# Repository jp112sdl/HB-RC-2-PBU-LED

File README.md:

# HB-RC-2-PBU-LED

**2 fach Wandtaster, ähnlich dem [HmIP-BSL](https://www.elv.de/elv-homematic-ip-schaltaktor-fuer-markenschalter-mit-signalleuchte-hmip-bsl.html), mit RGB LED Beleuchtung (oben/unten)).**

Thread im Homematic Forum: https://homematic-forum.de/forum/viewtopic.php?f=76&t=53254

### Bauteile
| Anzahl | Ref | Typ | Bezeichnung |
|----|----|----|----|
1 | U1 | AVR | [ATMega 328P-AU](https://www.reichelt.de/mcu-atmega-avr-risc-32-kb-20-mhz-tqfp-32-atmega-328p-au-p119684.html)
2 | R1, R2 | Widerstand 330 | [RND 0805 330](https://www.reichelt.de/smd-widerstand-0805-330-ohm-125-mw-1-rnd-0805-1-330-p183184.html)
2 | R3, R4 | Widerstand 10k | [RND 0805 10k](https://www.reichelt.de/smd-widerstand-0805-10-kohm-125-mw-1-rnd-0805-1-10k-p183251.html)
4 | C2, C4, C5, C7 |Kondensator 100n |[X7R-G0805 100N](https://www.reichelt.de/smd-vielschicht-keramikkondensator-100n-10-x7r-g0805-100n-p31879.html)
1 | C1 | ELKO 1µF/50V | [SMD ELKO 1,0/50](https://www.reichelt.de/smd-chip-elko-1-0-f-50volt-smd-elko-1-0-50-p31900.html)
2 | C3, C6 | ELKO 10µF/16V | [SMD ELKO 10/16](https://www.reichelt.de/smd-chip-elko-10-f-16volt-smd-elko-10-16-p31906.html)
1 | U2 | LDO | [TLV1117-33](https://www.reichelt.de/ldo-regler-fest-3-3-v-sot-223-4-tlv-1117-33-cdcy-p188993.html)
1 | D1 | DuoLED 3mm | [RND 135-00023](https://www.reichelt.de/led-3-mm-bedrahtet-rot-gruen-20-mcd-40-rnd-135-00023-p224130.html)
1 | U3 | LevelShifter | [SN74LVC1T45DBVR](https://www.aliexpress.com/item/32963167201.html)
1 | IC1 | 868MHz Funkmodul | [CC1101](https://www.aliexpress.com/item/32924239954.html)
1 | SW1, SW2, SW3 | Taster | [Tastersortiment](https://www.aliexpress.com/item/32811153729.html)
2 | |WS2812B LED Streifen | [NeoPixel-Stick-WS2812](https://www.amazon.de/NeoPixel-Stick-WS2812-5050-LEDs/dp/B019ZKN3XQ)

### PCB

### ein paar Bilder

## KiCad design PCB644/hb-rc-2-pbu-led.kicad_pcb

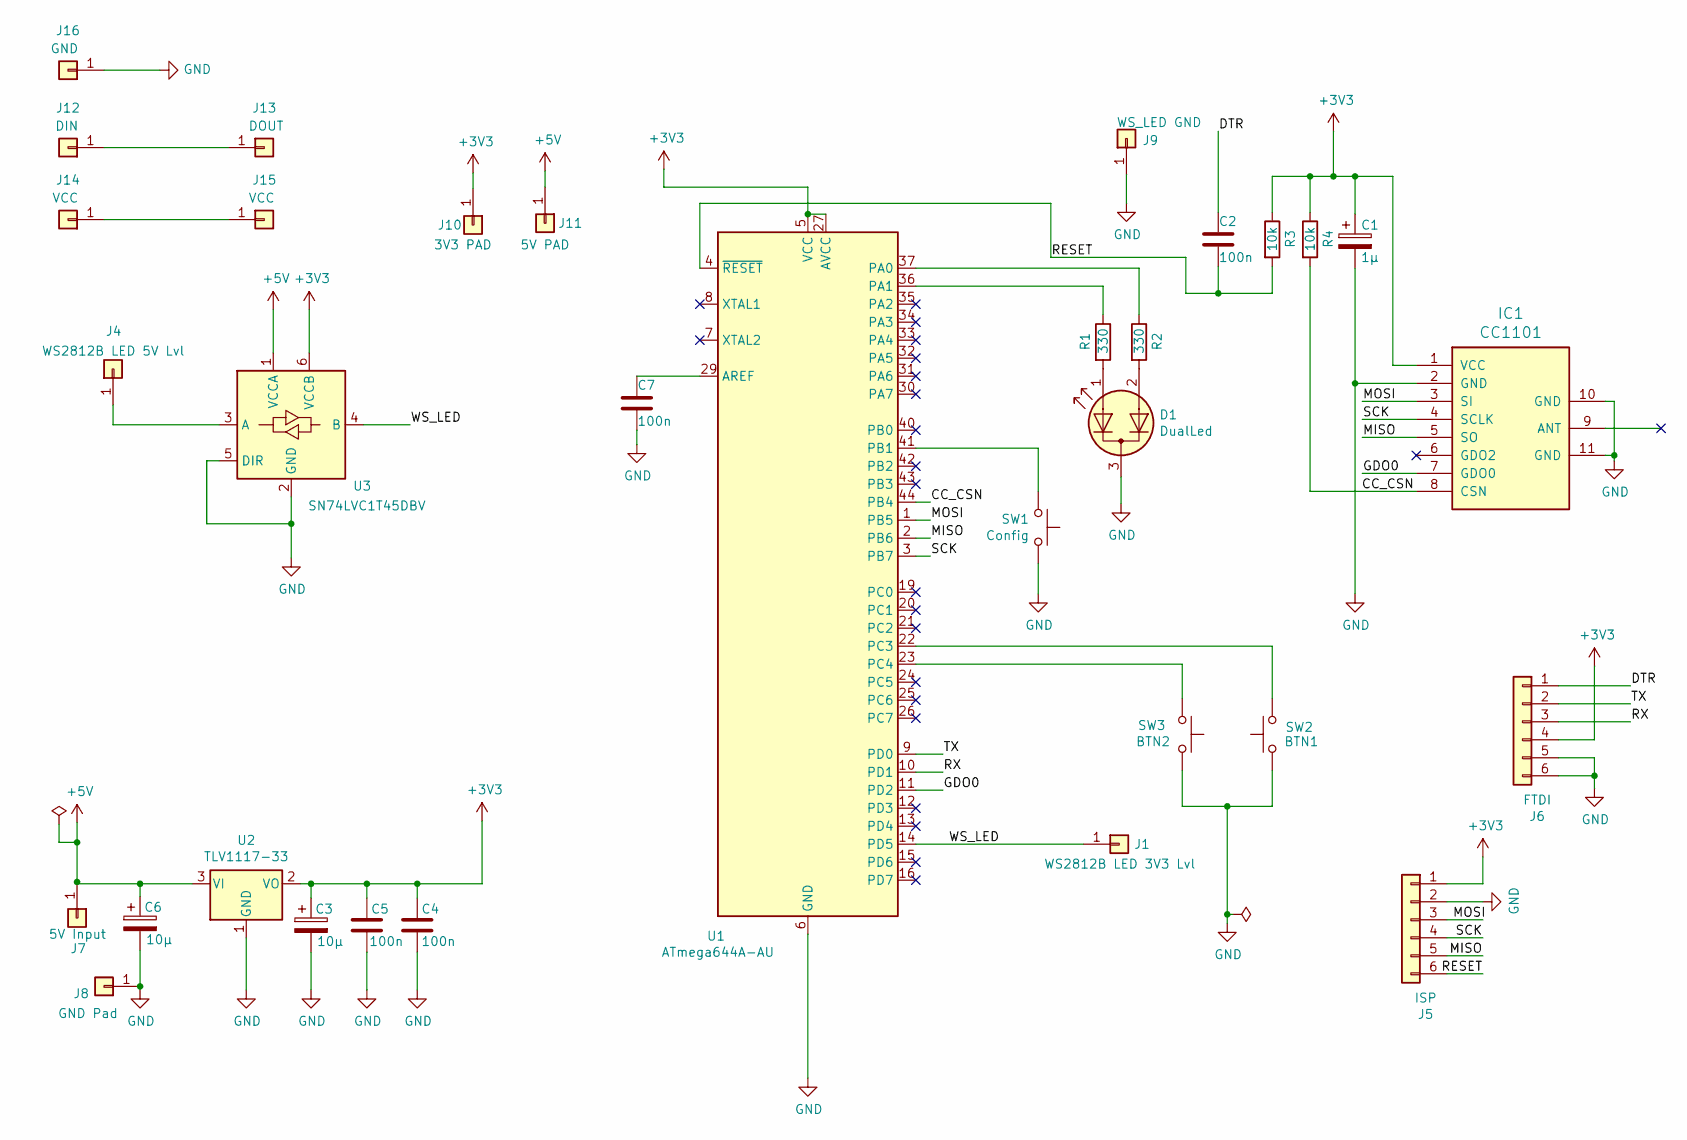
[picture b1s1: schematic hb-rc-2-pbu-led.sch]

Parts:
C1: 1µ; CP_Elec_4x5.3
C2, C4, C5, C7: 100n; C_0805_2012Metric_Pad1.15x1.40mm_HandSolder
C3, C6: 10µ; CP_Elec_4x5.4
D1: DualLed; LED_D3.0mm-3
IC1: CC1101; PinHeader_1x08_P2.00mm_Vertical
J1: WS2812B LED 3V3 Lvl; TestPoint_Pad_D2.0mm
J4: WS2812B LED 5V Lvl; TestPoint_Pad_D2.0mm
J5: ISP; PinHeader_1x06_P2.54mm_Vertical
J6: FTDI; PinHeader_1x06_P2.54mm_Vertical
J7: 5V Input; TestPoint_Pad_D2.0mm
J8: GND Pad; TestPoint_Pad_D2.0mm
J9: WS_LED GND; TestPoint_Pad_D2.0mm
J10: 3V3 PAD; TestPoint_Pad_D2.0mm
J11: 5V PAD; TestPoint_Pad_D2.0mm
J12: DIN; TestPoint_Pad_D2.0mm
J13: DOUT; TestPoint_Pad_D2.0mm
J14, J15: VCC; TestPoint_Pad_D2.0mm
J16: GND; TestPoint_Pad_D2.0mm
R1, R2: 330; R_0805_2012Metric_Pad1.15x1.40mm_HandSolder
R3, R4: 10k; R_0805_2012Metric_Pad1.15x1.40mm_HandSolder
SW1: Config; SW_SPST_FSMSM
SW2: BTN1; TO-126-2_Vertical
SW3: BTN2; TO-126-2_Vertical
U1: ATmega644A-AU; TQFP-44_10x10mm_P0.8mm
U2: TLV1117-33; SOT-223
U3: SN74LVC1T45DBV; SOT-23-6

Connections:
+3V3: C1.1, C3.1, C4.1, C5.1, IC1.1 (VCC), J5.1, J6.4, J10.1, R3.1, R4.1, U1.5 (VCC), U1.17 (VCC), U1.27 (AVCC), U1.38 (VCC), U2.2 (VO), U3.6 (VCCB)
+5V: C6.1, J7.1, J11.1, U2.3 (VI), U3.1 (VCCA)
/CC_CSN: IC1.8 (CSN), R4.2, U1.44 (PB4)
/DTR: C2.1, J6.1
/GDO0: IC1.7 (GDO0), U1.11 (PD2)
/MISO: IC1.5 (SO), J5.5, U1.2 (PB6)
/MOSI: IC1.3 (SI), J5.3, U1.1 (PB5)
/RESET: C2.2, J5.6, R3.2, U1.4 (~RESET)
/RX: J6.3, U1.10 (PD1)
/SCK: IC1.4 (SCLK), J5.4, U1.3 (PB7)
/TX: J6.2, U1.9 (PD0)
/WS_LED: J1.1, U1.14 (PD5), U3.4 (B)
GND: C1.2, C3.2, C4.2, C5.2, C6.2, C7.2, D1.3 (K), IC1.2 (GND), IC1.10 (GND), IC1.11 (GND), J5.2, J6.5, J6.6, J8.1, J9.1, J16.1, SW1.1, SW2.1, SW3.2, U1.6 (GND), U1.18 (GND), U1.28 (GND), U1.39 (GND), U2.1 (GND), U3.2 (GND), U3.5 (DIR)
unnamed: C7.1, U1.29 (AREF)
unnamed: D1.1 (A1), R1.2
unnamed: D1.2 (A2), R2.2
unnamed: J4.1, U3.3 (A)
unnamed: J12.1, J13.1
unnamed: J14.1, J15.1
unnamed: R1.1, U1.36 (PA1)
unnamed: R2.1, U1.37 (PA0)
unnamed: SW1.2, U1.41 (PB1)
unnamed: SW2.2, U1.22 (PC3)
unnamed: SW3.1, U1.23 (PC4)

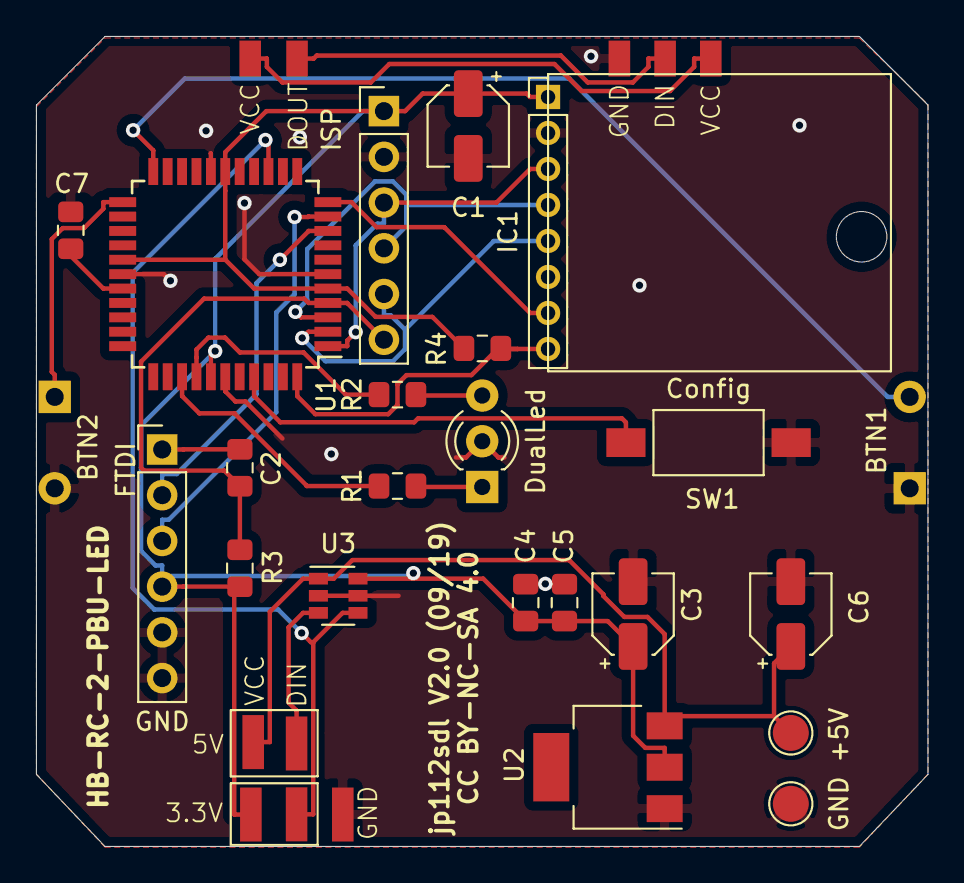
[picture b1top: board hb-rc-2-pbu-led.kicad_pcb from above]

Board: 2 copper layers, 49.5 x 45.0 mm, 33 parts (0 on the bottom side), 24 nets.

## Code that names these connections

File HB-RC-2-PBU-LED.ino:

//- -----------------------------------------------------------------------------------------------------------------------
// AskSin++
// 2019-08-26 jp112sdl Creative Commons - http://creativecommons.org/licenses/by-nc-sa/3.0/de/
//- -----------------------------------------------------------------------------------------------------------------------
// ci-test=yes board=328p aes=no

// define this to read the device id, serial and device type from bootloader section
// #define USE_OTA_BOOTLOADER

#define EI_NOTEXTERNAL
#include <EnableInterrupt.h>
#include <SPI.h>
#include <AskSinPP.h>
#include <LowPower.h>
#include <Register.h>
#include <MultiChannelDevice.h>
#include <FastLED.h>
#include <Remote.h>
#include <Dimmer.h>

//Pin Definitionen (when using 644P(A): use Standard Pinout)

#ifdef __AVR_ATmega328P__
#define CONFIG_BUTTON_PIN 8
#define WSLED_PIN         9      //GPIO Pin LED Anschluss
#define ONBOARD_LED_PIN1  14
#define ONBOARD_LED_PIN2  15
#define CC1101_CS         10
#define CC1101_GDO0       2
#define BTN1_PIN          16
#define BTN2_PIN          17
#endif

#ifdef __AVR_ATmega644P__
#define CONFIG_BUTTON_PIN 1       //PB1
#define WSLED_PIN         13      //PD5 GPIO Pin LED Anschluss
#define ONBOARD_LED_PIN1  25      //PA1
#define ONBOARD_LED_PIN2  24      //PA0
#define CC1101_CS         4       //PB4
#define CC1101_GDO0       10      //PD2
#define BTN1_PIN          19      //PC3
#define BTN2_PIN          20      //PC4
#endif


//Einstellungen für die RGB LEDs
#define WSNUM_LEDS    16          //Anzahl angeschlossener LEDs
#define WSLED_TYPE    WS2812B    //LED Typ
#define WSCOLOR_ORDER GRB        //Farbreihenfolge

uint8_t dim1level(0);
uint8_t dim2level(0);
uint8_t col1val(0);
uint8_t col2val(0);
CRGB leds[WSNUM_LEDS];


#define PEERS_PER_RGB_CHANNEL  3
#define PEERS_PER_RC_CHANNEL   12

using namespace as;

const struct DeviceInfo PROGMEM devinfo = {
  {0xF3, 0x30, 0x00},     // Device ID
  "JPRC2LED01",           // Device Serial
  {0xF3, 0x30},           // Device Model
  0x10,                   // Firmware Version
  as::DeviceType::Dimmer, // Device Type
  {0x01, 0x00}            // Info Bytes
};

typedef AskSin<DualStatusLed<ONBOARD_LED_PIN1, ONBOARD_LED_PIN2>, NoBattery, Radio<LibSPI<CC1101_CS>, CC1101_GDO0>> Hal;
Hal hal;

typedef RemoteChannel<Hal, PEERS_PER_RC_CHANNEL, DimmerList0> RemoteChannelType;
typedef DimmerChannel<Hal, PEERS_PER_RGB_CHANNEL,DimmerList0> RGBLEDChannelType;
typedef DimmerAndRemoteDevice<Hal, RGBLEDChannelType, RemoteChannelType, 4, 1, 2, DimmerList0> RCLEDDevice;

// we need no PWM class
class DummyPWM {
public:
  void init(uint8_t __attribute__ ((unused)) pwm) {}
  void set(uint8_t __attribute__ ((unused)) pwm) {}
  void param(uint8_t __attribute__ ((unused)) speedMultiplier, uint8_t __attribute__ ((unused)) characteristic) {}
};

template<class HalType,class DimmerType,class PWM>
class RGBControl : public DimmerControl<HalType,DimmerType,PWM> {
public:
  typedef DimmerControl<HalType,DimmerType,PWM> BaseControl;
  RGBControl (DimmerType& dim) : BaseControl(dim) {
    for (int i = 0; i < WSNUM_LEDS; i++) {
      leds[i] = CRGB::Black;
    }
    FastLED.addLeds<WSLED_TYPE, WSLED_PIN, WSCOLOR_ORDER>(leds, WSNUM_LEDS);
    FastLED.setBrightness(255);
  }

  virtual ~RGBControl () {}

  virtual void updatePhysical () {
    // first calculate all physical values of the dimmer channels
    BaseControl::updatePhysical();
    // set brightness and color to LEDs
    uint8_t ledprocombi = WSNUM_LEDS / (this->physicalCount() / 2);
    uint8_t ledidx = 0;
    for( uint8_t i=0; i<this->physicalCount();  ) {
      uint8_t dimlevel = this->physical[i++];
      uint8_t collevel = this->physical[i++];
      CRGB ledvalue = CHSV((collevel * 1275L) / 1000, (collevel <  200) ? 255 : 0, dimlevel);
      // set to real LEDs
      for( uint8_t y=0; y<ledprocombi; ++y) {
        leds[ledidx++] = ledvalue;
      }
    }
    FastLED.show();
  }
};

RCLEDDevice sdev(devinfo, 0x20);
RGBControl<Hal,RCLEDDevice,DummyPWM> control(sdev);
ConfigButton<RCLEDDevice> cfgBtn(sdev);

void setup () {
  DINIT(57600, ASKSIN_PLUS_PLUS_IDENTIFIER);
  uint8_t pins[4] = {0,0,0,0}; // all 4 PWM pins are 0
  control.init(hal,pins);
  remoteChannelISR(sdev.remoteChannel(1), BTN1_PIN);
  remoteChannelISR(sdev.remoteChannel(2), BTN2_PIN);
  buttonISR(cfgBtn, CONFIG_BUTTON_PIN);
  sdev.initDone();
}

void loop() {
  bool worked = hal.runready();
  bool poll = sdev.pollRadio();
  if ( worked == false && poll == false ) {
    hal.activity.savePower<Idle<true>>(hal);
  }
}

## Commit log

2019-08-26 add image
2019-08-28 replaced image
2019-08-30 cleanup
2019-09-01 fit in 328p eeprom
2019-09-01 use 16 ws2812b leds
2019-09-10 add gerber
2019-09-10 add pcb
2019-09-10 add cc1101
2019-09-10 pcb update
2019-09-10 update images
2019-09-10 images
2019-09-10 changed images
2019-09-10 image
2019-09-12 fixed wrong ws2812b pin order
2019-09-18 fixed missing GND connections
2019-09-18 changed image
2019-09-19 use native Dimmer
2019-09-20 save some sketch size
2019-09-20 fex missing GND connections
2019-09-20 add pcb for atmega644
2019-09-20 update pcb files
2019-09-26 new pcb image
2020-07-26 add pin definitions for ATmega 644P(A)
2021-02-16 update ci test
2021-02-16 update for asksinpp lib comaptibility
2021-02-16 fix compiler error

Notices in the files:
PCB644/hb-rc-2-pbu-led.kicad_pcb:
CC BY-NC-SA 4.0
